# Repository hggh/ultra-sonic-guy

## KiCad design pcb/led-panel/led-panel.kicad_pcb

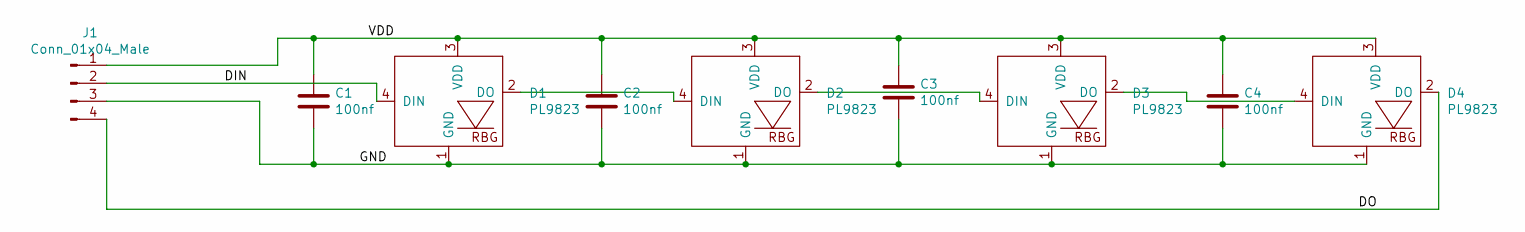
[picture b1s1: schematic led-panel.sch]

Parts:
C1, C2, C3, C4: 100nf; C_0805_2012Metric
D1, D2, D3, D4: PL9823; PL9823-F5
J1: Conn_01x04_Male; PinHeader_1x04_P2.00mm_Vertical

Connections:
/DIN: D1.4 (DIN), J1.2
/DO: D4.2 (DO), J1.4
/GND: C1.2, C2.2, C3.2, C4.2, D1.1 (GND), D2.1 (GND), D3.1 (GND), D4.1 (GND), J1.3
/VDD: C1.1, C2.1, C3.1, C4.1, D1.3 (VDD), D2.3 (VDD), D3.3 (VDD), D4.3 (VDD), J1.1
unnamed: D1.2 (DO), D2.4 (DIN)
unnamed: D2.2 (DO), D3.4 (DIN)
unnamed: D3.2 (DO), D4.4 (DIN)

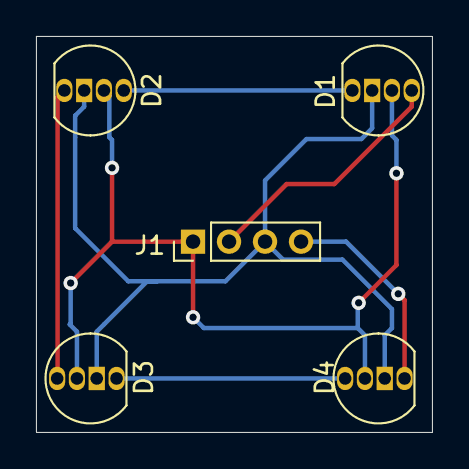
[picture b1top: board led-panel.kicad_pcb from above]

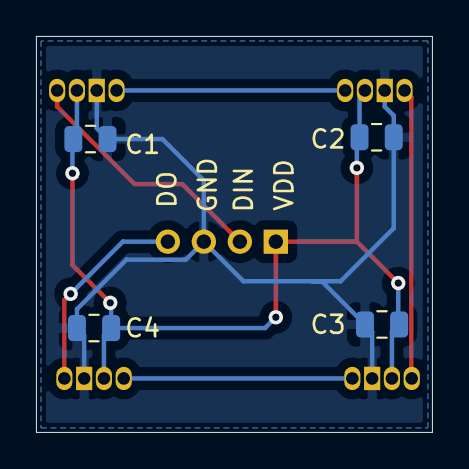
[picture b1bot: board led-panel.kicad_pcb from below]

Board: 2 copper layers, 22.0 x 22.0 mm, 9 parts (4 on the bottom side), 7 nets.

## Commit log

2020-12-05 initial
2020-12-05 basic code
2020-12-11 add led holder 5mm PL
2020-12-11 update test code
2020-12-12 add arms and legs
2020-12-12 update drawing for test sizes
2020-12-12 migrate into one scad file
2020-12-12 update code
2020-12-14 more colors
2020-12-27 update case
2020-12-30 update arm
2021-04-08 add pcb
